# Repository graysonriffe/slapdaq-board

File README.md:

# SlapDAQ Board

This is the KiCad project for the SlapDAQ PCB.

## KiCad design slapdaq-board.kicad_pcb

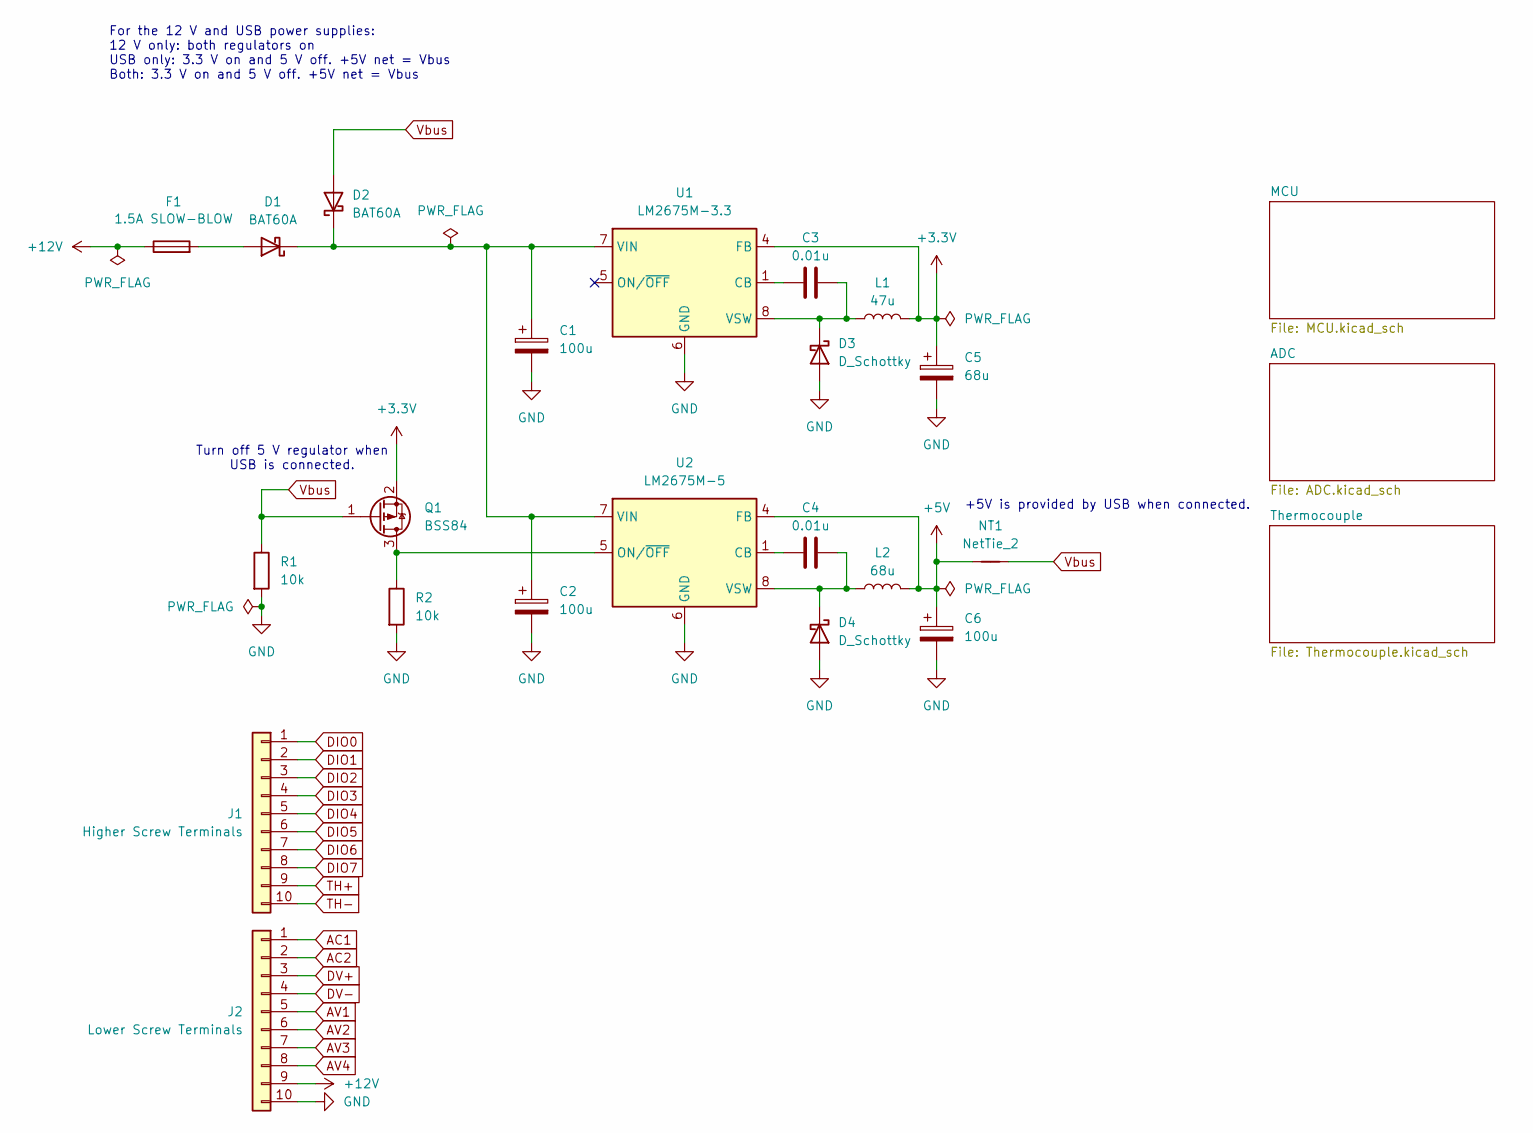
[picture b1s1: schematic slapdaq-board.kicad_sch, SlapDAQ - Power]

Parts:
C1, C2: 100u; CP_EIA-7260-38_AVX-R_HandSolder; MPN 594D107X9025R2T
C3, C4: 0.01u; C_1206_3216Metric_Pad1.33x1.80mm_HandSolder; MPN GRM31CR73A103KW03L
C5: 68u; CP_EIA-7132-28_AVX-C_HandSolder; MPN 594D686X9010C2T
C6: 100u; CP_EIA-7132-28_AVX-C_HandSolder; MPN 594D107X9016C2T
D1, D2: BAT60A; D_SOD-323; MPN BAT60AE6327HTSA1
D3, D4: D_Schottky; D_SMA_Handsoldering; MPN SK13
F1: 1.5A SLOW-BLOW; Fuse_1206_3216Metric_Pad1.42x1.75mm_HandSolder; MPN SF-1206S150M-2
J1: Higher Screw Terminals; CONN_SD-39512-001_10P_MOL; MPN 39512-6010
J2: Lower Screw Terminals; CONN_SD-39512-001_10P_MOL; MPN 39512-6010
L1: 47u; L_Fastron_PISN_Handsoldering; MPN DO3316P-473MLD
L2: 68u; L_Fastron_PISN_Handsoldering; MPN DO3316P-683MLD
NT1: NetTie_2; NetTie-2_SMD_Pad0.5mm
Q1: BSS84; SOT-23; MPN BSS84AK,215
R1, R2: 10k; R_1206_3216Metric_Pad1.30x1.75mm_HandSolder; MPN RC1206DR-0710KL
U1: LM2675M-3.3; SOIC-8_3.9x4.9mm_P1.27mm; MPN LM2675MX-3.3/NOPB
U2: LM2675M-5; SOIC-8_3.9x4.9mm_P1.27mm; MPN LM2675MX-5.0/NOPB

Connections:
+3.3V: C5.1, L1.2, Q1.2 (S), U1.4 (FB); also elsewhere on the board
+5V: C6.1, L2.2, NT1.1, U2.4 (FB); also elsewhere on the board
+12V: F1.1, J2.9
AC1: J2.1; also elsewhere on the board
AC2: J2.2; also elsewhere on the board
AV1: J2.5; also elsewhere on the board
AV2: J2.6; also elsewhere on the board
AV3: J2.7; also elsewhere on the board
AV4: J2.8; also elsewhere on the board
DIO0: J1.1; also elsewhere on the board
DIO1: J1.2; also elsewhere on the board
DIO2: J1.3; also elsewhere on the board
DIO3: J1.4; also elsewhere on the board
DIO4: J1.5; also elsewhere on the board
DIO5: J1.6; also elsewhere on the board
DIO6: J1.7; also elsewhere on the board
DIO7: J1.8; also elsewhere on the board
DV+: J2.3; also elsewhere on the board
DV-: J2.4; also elsewhere on the board
GND: C1.2, C2.2, C5.2, C6.2, D3.2 (A), D4.2 (A), J2.10, R1.2, R2.2, U1.6 (GND), U2.6 (GND); also elsewhere on the board
unnamed: D1.2 (A), F1.2
unnamed: C1.1, C2.1, D1.1 (K), D2.1 (K), U1.7 (VIN), U2.7 (VIN)
unnamed: C3.2, D3.1 (K), L1.1, U1.8 (VSW)
unnamed: C4.2, D4.1 (K), L2.1, U2.8 (VSW)
unnamed: Q1.3 (D), R2.1, U2.5 (ON/~OFF)
unnamed: C3.1, U1.1 (CB)
unnamed: C4.1, U2.1 (CB)
TH+: J1.9; also elsewhere on the board
TH-: J1.10; also elsewhere on the board
Vbus: D2.2 (A), NT1.2, Q1.1 (G), R1.1; also elsewhere on the board

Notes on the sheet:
Turn off 5 V regulator when USB is connected.
For the 12 V and USB power supplies: 12 V only: both regulators on USB only: 3.3 V on and 5 V off. +5V net = Vbus Both: 3.3 V on and 5 V off. +5V net = Vbus
+5V is provided by USB when connected.

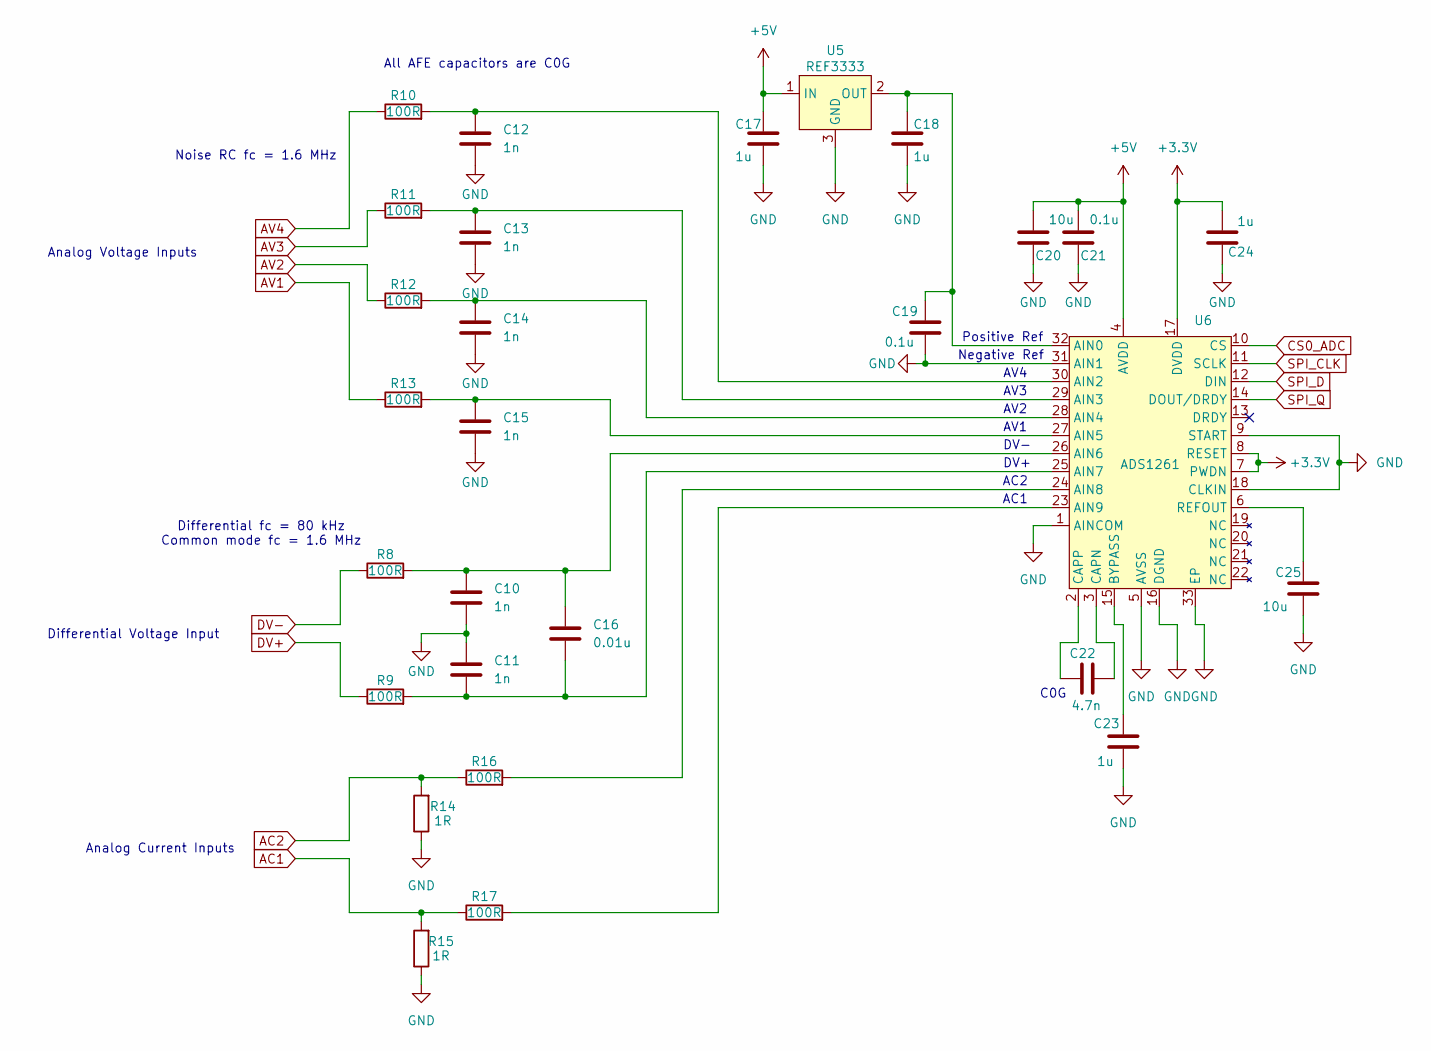
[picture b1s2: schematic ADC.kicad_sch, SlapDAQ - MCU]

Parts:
C10, C11, C12, C13, C14, C15: 1n; C_1206_3216Metric_Pad1.33x1.80mm_HandSolder; MPN GRM31C5C3A102JWA3L
C16: 0.01u; C_1206_3216Metric_Pad1.33x1.80mm_HandSolder; MPN GRM31C5C2J103JWA3L
C17, C18, C23, C24: 1u; C_1206_3216Metric_Pad1.33x1.80mm_HandSolder; MPN GRM31CR71E105KA01L
C19, C21: 0.1u; C_1206_3216Metric_Pad1.33x1.80mm_HandSolder; MPN GRM31CR72E104KW03L
C20, C25: 10u; C_1206_3216Metric_Pad1.33x1.80mm_HandSolder; MPN GCM31CC71E106KA03K
C22: 4.7n; C_1206_3216Metric_Pad1.33x1.80mm_HandSolder; MPN GCM3195C2A472FA16D
R8, R9, R10, R11, R12, R13, R16, R17: 100R; R_1206_3216Metric_Pad1.30x1.75mm_HandSolder; MPN RC1206DR-07100RL
R14, R15: 1R; R_1206_3216Metric_Pad1.30x1.75mm_HandSolder; MPN AC1206FR-071RL
U5: REF3333; SOT-23; MPN REF3333AIDBZR
U6: ADS1261; QFN-32-1EP_5x5mm_P0.5mm_EP3.45x3.45mm_ThermalVias; MPN ADS1261IRHBT

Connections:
+3.3V: C24.2, U6.7 (PWDN), U6.8 (RESET), U6.17 (DVDD); also elsewhere on the board
+5V: C17.1, C20.2, C21.2, U5.1 (IN), U6.4 (AVDD); also elsewhere on the board
AC1: R15.2, R17.1; also elsewhere on the board
AC2: R14.2, R16.1; also elsewhere on the board
AV1: R13.1; also elsewhere on the board
AV2: R12.1; also elsewhere on the board
AV3: R11.1; also elsewhere on the board
AV4: R10.1; also elsewhere on the board
CS0_ADC: U6.10 (CS); also elsewhere on the board
DV+: R9.1; also elsewhere on the board
DV-: R8.1; also elsewhere on the board
GND: C10.2, C11.1, C12.2, C13.2, C14.2, C15.2, C17.2, C18.2, C19.2, C20.1, C21.1, C23.2, C24.1, C25.2, R14.1, R15.1, U5.3 (GND), U6.1 (AINCOM), U6.5 (AVSS), U6.9 (START), U6.16 (DGND), U6.18 (CLKIN), U6.31 (AIN1), U6.33 (EP); also elsewhere on the board
unnamed: C18.1, C19.1, U5.2 (OUT), U6.32 (AIN0)
unnamed: C12.1, R10.2, U6.30 (AIN2)
unnamed: C13.1, R11.2, U6.29 (AIN3)
unnamed: C14.1, R12.2, U6.28 (AIN4)
unnamed: C15.1, R13.2, U6.27 (AIN5)
unnamed: C10.1, C16.1, R8.2, U6.26 (AIN6)
unnamed: C11.2, C16.2, R9.2, U6.25 (AIN7)
unnamed: R16.2, U6.24 (AIN8)
unnamed: R17.2, U6.23 (AIN9)
unnamed: C23.1, U6.15 (BYPASS)
unnamed: C22.2, U6.3 (CAPN)
unnamed: C22.1, U6.2 (CAPP)
unnamed: C25.1, U6.6 (REFOUT)
SPI_CLK: U6.11 (SCLK); also elsewhere on the board
SPI_D: U6.12 (DIN); also elsewhere on the board
SPI_Q: U6.14 (DOUT/DRDY); also elsewhere on the board

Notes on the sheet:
AC1
Positive Ref
Negative Ref
Noise RC fc = 1.6 MHz
AV4
Differential fc = 80 kHz Common mode fc = 1.6 MHz
Analog Current Inputs
AV1
AC2
Analog Voltage Inputs
AV3
All AFE capacitors are C0G
DV+
DV-
Differential Voltage Input
AV2
C0G

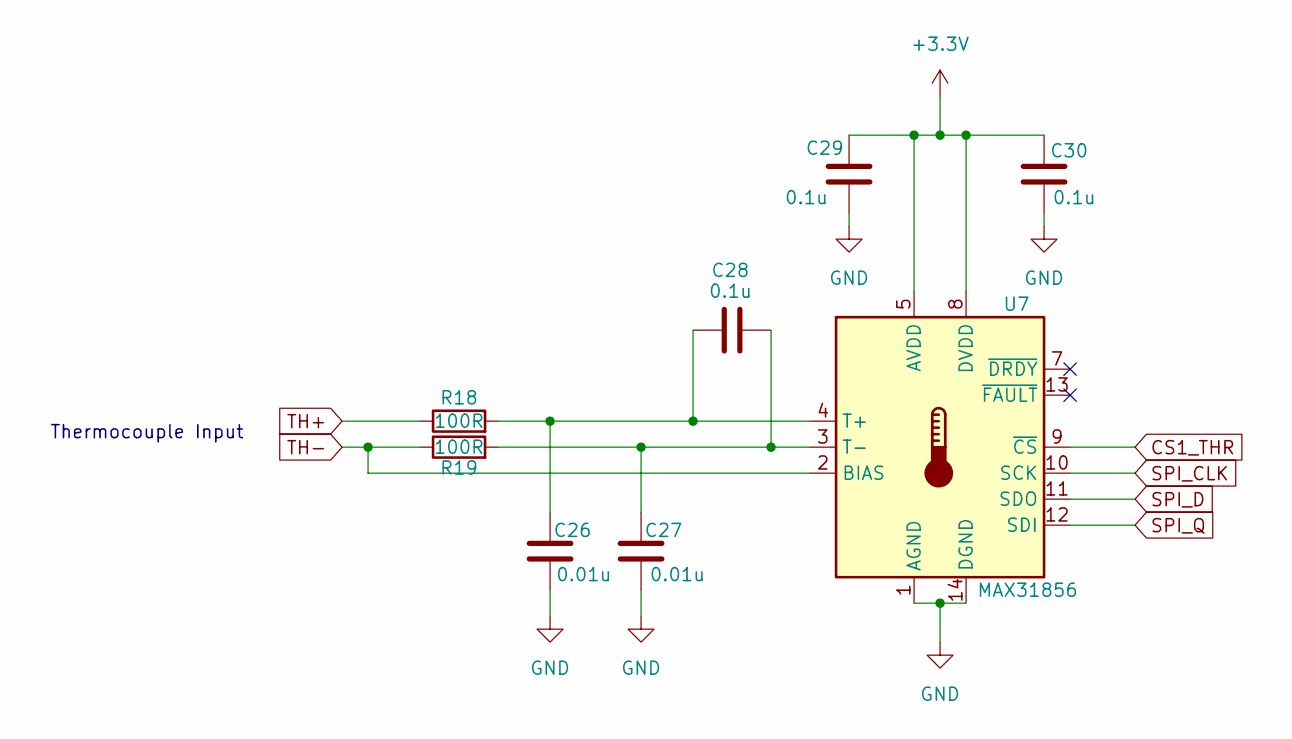
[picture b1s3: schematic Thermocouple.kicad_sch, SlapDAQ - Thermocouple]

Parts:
C26, C27: 0.01u; C_1206_3216Metric_Pad1.33x1.80mm_HandSolder; MPN GRM31CR73A103KW03L
C28, C29, C30: 0.1u; C_1206_3216Metric_Pad1.33x1.80mm_HandSolder; MPN GRM31CR72E104KW03L
R18, R19: 100R; R_1206_3216Metric_Pad1.30x1.75mm_HandSolder; MPN RC1206DR-07100RL
U7: MAX31856; TSSOP-14_4.4x5mm_P0.65mm; MPN MAX31856MUD+

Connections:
+3.3V: C29.1, C30.1, U7.5 (AVDD), U7.8 (DVDD); also elsewhere on the board
CS1_THR: U7.9 (~CS); also elsewhere on the board
GND: C26.2, C27.2, C29.2, C30.2, U7.1 (AGND), U7.14 (DGND); also elsewhere on the board
unnamed: C26.1, C28.1, R18.2, U7.4 (T+)
unnamed: C27.1, C28.2, R19.2, U7.3 (T-)
SPI_CLK: U7.10 (SCK); also elsewhere on the board
SPI_D: U7.11 (SDO); also elsewhere on the board
SPI_Q: U7.12 (SDI); also elsewhere on the board
TH+: R18.1; also elsewhere on the board
TH-: R19.1, U7.2 (BIAS); also elsewhere on the board

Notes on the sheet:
Thermocouple Input

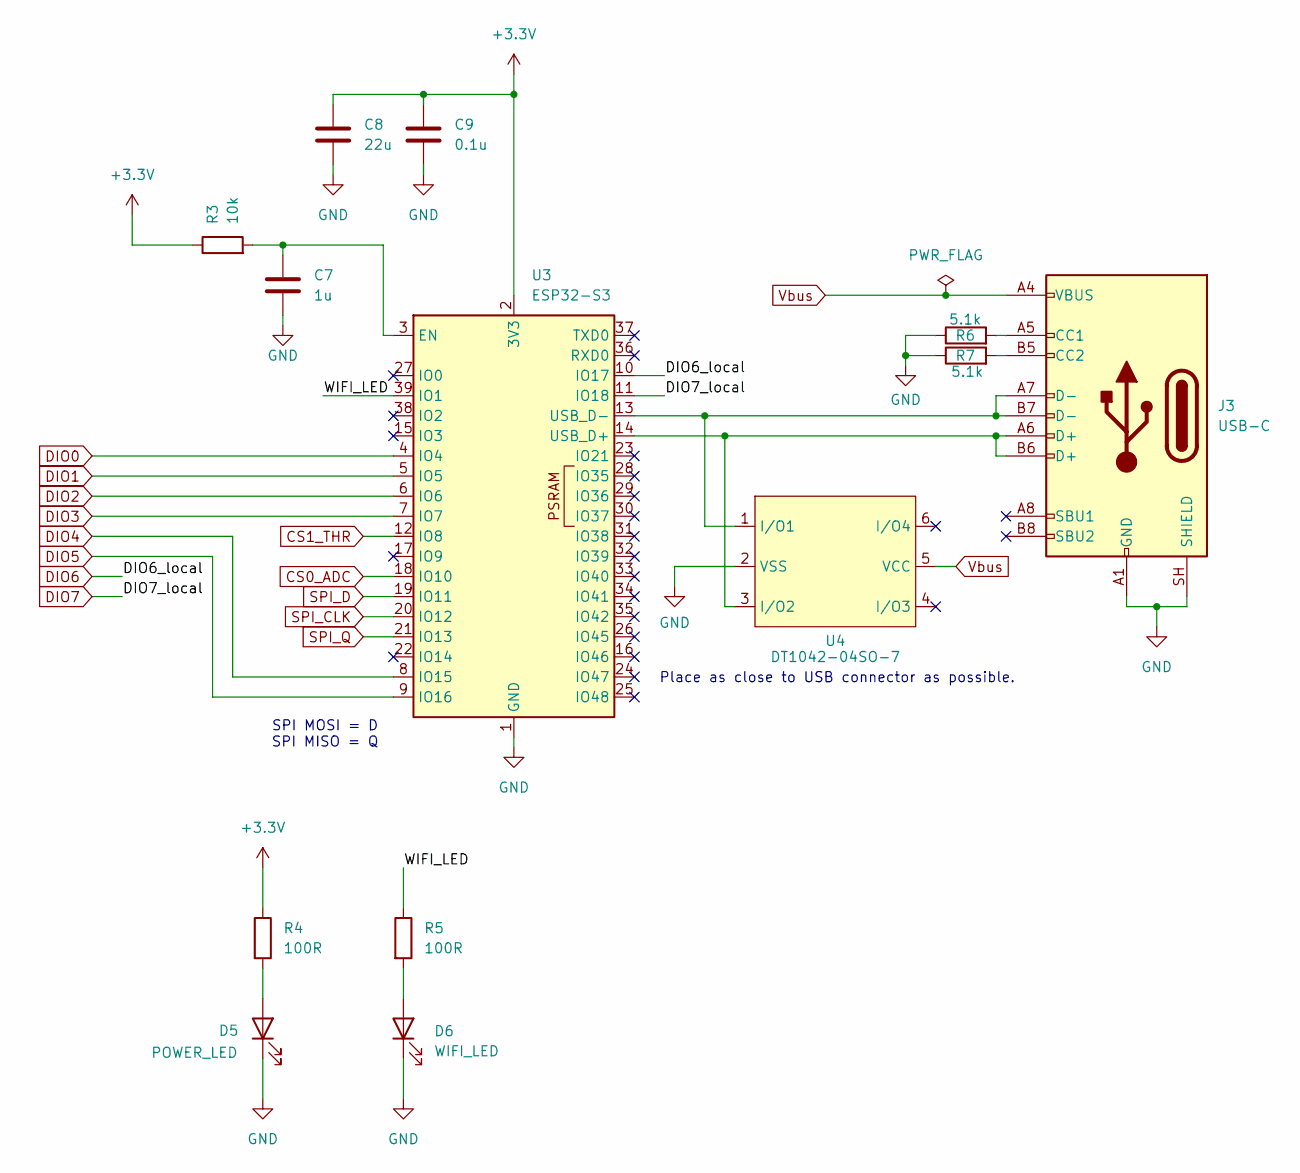
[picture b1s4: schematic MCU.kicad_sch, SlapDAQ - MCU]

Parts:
C7: 1u; C_1206_3216Metric_Pad1.33x1.80mm_HandSolder; MPN GRM31CR71E105KA01L
C8: 22u; C_1206_3216Metric_Pad1.33x1.80mm_HandSolder; MPN GCM31CR71A226KE02L
C9: 0.1u; C_1206_3216Metric_Pad1.33x1.80mm_HandSolder; MPN GRM31CR72E104KW03L
D5: POWER_LED; LED_D5.0mm_Horizontal_O1.27mm_Z3.0mm; MPN WP7113ID
D6: WIFI_LED; LED_D5.0mm_Horizontal_O1.27mm_Z3.0mm; MPN WP7113YD
J3: USB-C; USB_C_Receptacle_GCT_USB4110; MPN USB4110-GF-A
R3: 10k; R_1206_3216Metric_Pad1.30x1.75mm_HandSolder; MPN RC1206DR-0710KL
R4, R5: 100R; R_1206_3216Metric_Pad1.30x1.75mm_HandSolder; MPN RC1206DR-07100RL
R6, R7: 5.1k; R_1206_3216Metric_Pad1.30x1.75mm_HandSolder; MPN AC1206FR-075K1L
U3: ESP32-S3; ESP32-S3-WROOM-1; MPN ESP32-S3-WROOM-1-N16R8
U4: DT1042-04SO-7; SOT-23-6; MPN DT1042-04SOQ-7

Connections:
+3.3V: C8.2, C9.2, R3.1, R4.1, U3.2 (3V3); also elsewhere on the board
/MCU/WIFI_LED: R5.1, U3.39 (IO1)
CS0_ADC: U3.18 (IO10); also elsewhere on the board
CS1_THR: U3.12 (IO8); also elsewhere on the board
DIO0: U3.4 (IO4); also elsewhere on the board
DIO1: U3.5 (IO5); also elsewhere on the board
DIO2: U3.6 (IO6); also elsewhere on the board
DIO3: U3.7 (IO7); also elsewhere on the board
DIO4: U3.8 (IO15); also elsewhere on the board
DIO5: U3.9 (IO16); also elsewhere on the board
DIO6: U3.10 (IO17); also elsewhere on the board
DIO7: U3.11 (IO18); also elsewhere on the board
GND: C7.2, C8.1, C9.1, D5.1 (K), D6.1 (K), J3.A1 (GND), J3.A12 (GND), J3.B1 (GND), J3.B12 (GND), J3.SH (SHIELD), R6.1, R7.1, U3.1 (GND), U3.40 (GND), U3.41 (GND), U4.2 (VSS); also elsewhere on the board
unnamed: D5.2 (A), R4.2
unnamed: D6.2 (A), R5.2
unnamed: J3.A5 (CC1), R6.2
unnamed: J3.B5 (CC2), R7.2
unnamed: C7.1, R3.2, U3.3 (EN)
unnamed: J3.A6 (D+), J3.B6 (D+), U3.14 (USB_D+), U4.3 (I/O2)
unnamed: J3.A7 (D-), J3.B7 (D-), U3.13 (USB_D-), U4.1 (I/O1)
SPI_CLK: U3.20 (IO12); also elsewhere on the board
SPI_D: U3.19 (IO11); also elsewhere on the board
SPI_Q: U3.21 (IO13); also elsewhere on the board
Vbus: J3.A4 (VBUS), J3.A9 (VBUS), J3.B4 (VBUS), J3.B9 (VBUS), U4.5 (VCC); also elsewhere on the board

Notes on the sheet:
SPI MOSI = D SPI MISO = Q
Place as close to USB connector as possible.

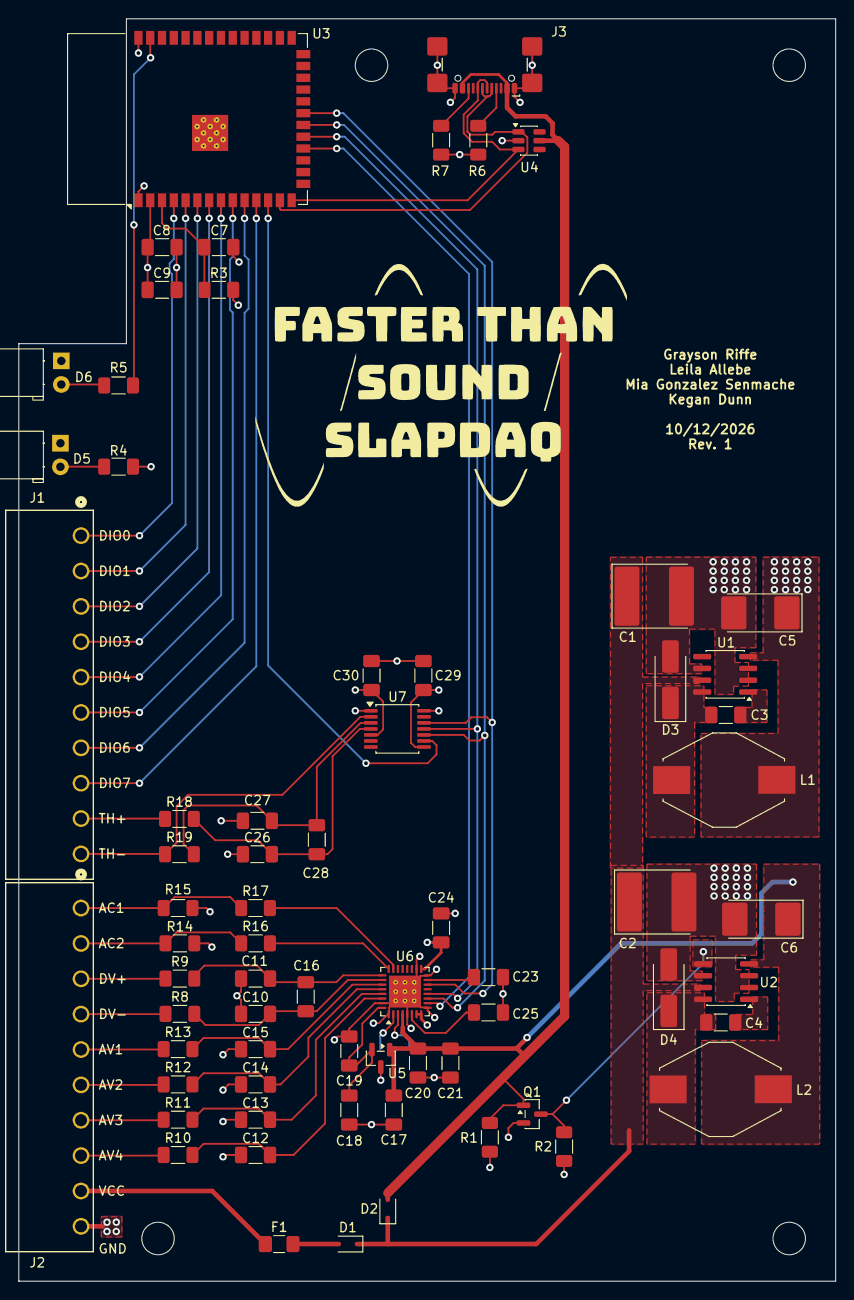
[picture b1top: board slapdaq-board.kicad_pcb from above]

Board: 4 copper layers, 88.0 x 136.0 mm, 70 parts (1 on the bottom side), 58 nets.
